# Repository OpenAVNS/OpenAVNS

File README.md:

# OpenAVNS

## Purpose
To develop an open-source, open-architecture auricular vagus nerve stimulator under a distributed development model.
 
Auricular vagus nerve stimulation (aVNS) is a method of neuromodulation that uses electrical pulses applied to nerves near the ear to create a vagus nerve response. This response can lead to reduced sympathetic (fight or flight) and increased parasympathetic (relaxation / everything ok) tone. Adjusting vagal tone using aVNS has been explored by clinical researchers for a number of potential therapeutic applications, including for depression [1], opioid withdraws [2], chronic pain [3], and gastrointestinal issues [4]. In addition, aVNS has been explored in wellness for applications such as stress reduction [5]. We believe an open-source, open-architecture aVNS system would be helpful for users, students, medical researchers, and community members around the world to explore aVNS and to learn more about developing neuromodulation devices under an open source model.
 
1. [Tan, Chaoren et. al. 2023](https://pubmed.ncbi.nlm.nih.gov/37230264/)  
2. [Tirado, Carlos F. et. al. 2022](https://pmc.ncbi.nlm.nih.gov/articles/PMC9385243/)  
3. [Duff, Irina T. et. al. 2024](https://pmc.ncbi.nlm.nih.gov/articles/PMC11543973/)  
4. [Veldman, Fleur et. al. 2025](https://pmc.ncbi.nlm.nih.gov/articles/PMC11769675/)  
5. [Sanches-Perez, Jesus et. al. 2023](https://pmc.ncbi.nlm.nih.gov/articles/PMC10512834/)  

## Principles of OpenAVNS
* _Openness_ – all source files, including code, PCB source files, CAD, and any documentation, available under permissive license
* _Accessibility_ – device developed using freely available tools (KiCad for PCBs, FreeCAD for enclosure, etc.); enclosure able to be 3D printed on home printer; PCBs use only common, off the shelf components and able to be taped out and assembled by a low-cost manufacturer; clear instructions are developed for building, flashing, and testing a device; low-cost, replaceable, commercially available electrodes are used to apply stimulation; apps should be developed on a platform that allows iOS and Android releases simultaneously
* _Wearability_ – device should be as small and unobtrusive as possible while maintaining openness and accessibility. Ideally, all electronics would fit behind the ear (similar to a behind-ear hearing aid or cochlear implant electronics) and can be comfortably worn for at least 30 minutes at a time
* _Effectiveness_ – the device should be capable of outputting stimulation with the same parameters as those used in clinical trials for at least 30 minutes. We note that OpenAVNS cannot be considered to be “effective” for any indication until it has been tested in a clinical trial.
* _Safety_ – the device’s electronics, firmware, software, and mechanical design should all be constructed with user safety in mind, and should be built to the standards of a medical device. We note that until OpenAVNS has been tested and cleared by a regulatory body for human use it cannot be considered “safe”; any use of the source files and documentation in the project must be done for educational purposes only and is done entirely at the user’s own risk. PLEASE DO NOT HURT YOURSELF!
 
## Proposed user needs and design inputs
| User Need | Design Input |
|-----------|--------------|
| The device shall apply neuromodulation to the auricular vagus branches at the tragus and cymba concha | Device shall provide two independent biphasic current-controlled stimulation outputs |
| The user shall easily activate, modify, and deactivate stimulation on the device | App shall allow adjustment of stimulation parameters (frequency, pulse width, amplitude) within specified ranges. <br><br> App shall allow initiating and stopping stimulation <br><br> Physical button on device to deactivate stimulation if needed <br><br> App shall be intuitive and easy to use |
| The user shall comfortably wear the device | Weight less than 40g <br><br> Device fits behind ear <br><br> Remains securely in place for 30 minutes of typical non-athletic activity without discomfort |
| The user shall apply neuromodulation typical of clinical studies reported in literature | Adjustable outputs between 1-50Hz, 100-500us pulse width, 0-2mA amplitude <br><br> Capable of outputting at maximum settings on one channel for a minimum of 30min |
| The device is open and accessible to a large range of users in different situations | Rechargeable by USB-C <br><br> Uses commercial off the shelf replaceable electrodes <br><br> App available on iOS and Android platforms |
| The device is safe to use | Device hardware prevents DC charge or amplitudes outside of the operating parameters from presenting at the electrode sites <br><br> Physical button on device to stop stimulation <br><br> Impedance measurement on output used to stop stimulation if electrodes are disconnected (short or open circuit) <br><br> Stimulation stops if wireless connection to app is interrupted <br><br> Firmware automatically stops stimulation after 30min regardless of other factors |

## Project Goals / Timeline
_2025_
* _August:_ set up project structure, onboard contributors, assign tasks, generate block diagrams of system
* _September:_ design and tape out first version of PCB, develop test firmware, generate proof of concept drawings / mock-ups for enclosure and user interface
* _October:_ test and document initial PCB and firmware for power draw, output integrity, and safety, develop initial app prototype, combine board needs and enclosure drawings to create CAD model
* _November:_ tape out second version of PCB designed for enclosure, conduct fit test, create alpha version of iOS and Android app
* _December:_ first system tests of prototype device (HW + FW + Enclosure + App)

## Contributors
Last updated 10/31/2025
* [Alex Baldwin](https://www.linkedin.com/in/alexbbaldwin/) - Founder, PCB schematics and layout
* [Amanda Cheung](https://www.linkedin.com/in/amandacheung8/) - Enclosure CAD
* [Maro Michailidou](https://www.linkedin.com/in/maro-michailidou/) - PCB Layout Review

## Disclaimer
The contents of this document, the OpenAVNS repository on GitHub, and any other documents or communication released by the OpenAVNS project (the “Materials”) are subject to revision. No representation or warranty, express or implied, is provided in relation to the accuracy, correctness, completeness, or reliability of the information, opinions, or conclusions expressed in this repository.

The Materials are experimental in nature and should be used with prudence and appropriate caution. Any use is voluntary and at your own risk.

The Materials are made available “as is” by the contributors to this repository (collectively, “Providers”). Providers expressly disclaim all warranties, express or implied, arising in connection with the Materials, or arising out of a course of performance, dealing, or trade usage, including, without limitation, any warranties of title, noninfringement, merchantability, or fitness for a particular purpose.

Any user of the Materials agrees to forever indemnify, defend, and hold harmless Providers from and against, and to waive any and all claims against Providers for any and all claims, suits, demands, liability, loss or damage whatsoever, including attorneys' fees, whether direct or consequential, on account of any loss, injury, death or damage to any person or (including without limitation all agents and employees of Providers and all property owned by, leased to or used by either Providers) or on account of any loss or damages to business or reputations or privacy of any persons, arising in whole or in part in any way from use of the Materials or in any way connected therewith or in any way related thereto.

The Materials, any related materials, and all intellectual property therein, are owned by Providers.

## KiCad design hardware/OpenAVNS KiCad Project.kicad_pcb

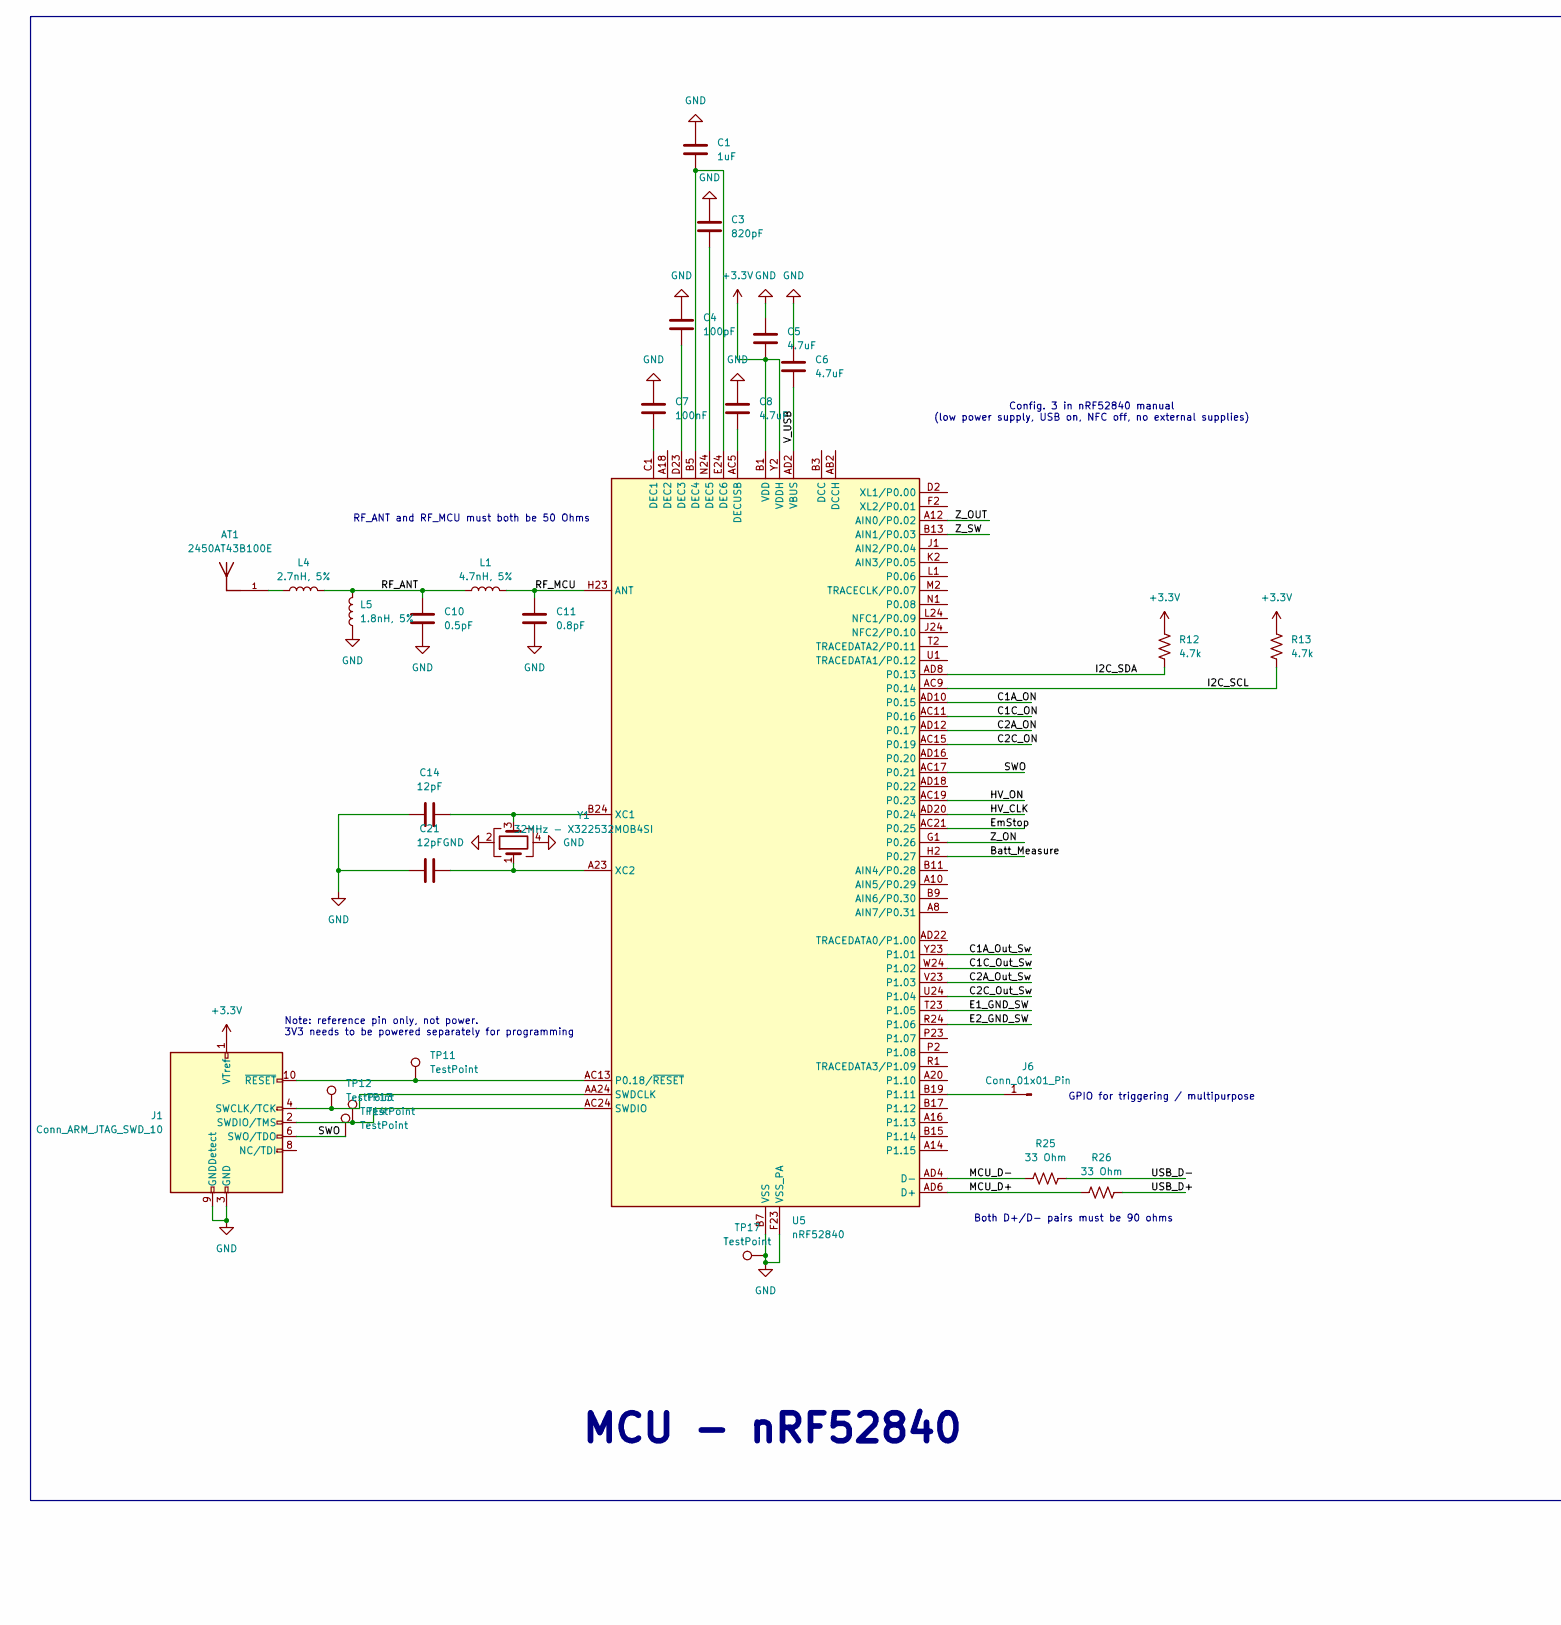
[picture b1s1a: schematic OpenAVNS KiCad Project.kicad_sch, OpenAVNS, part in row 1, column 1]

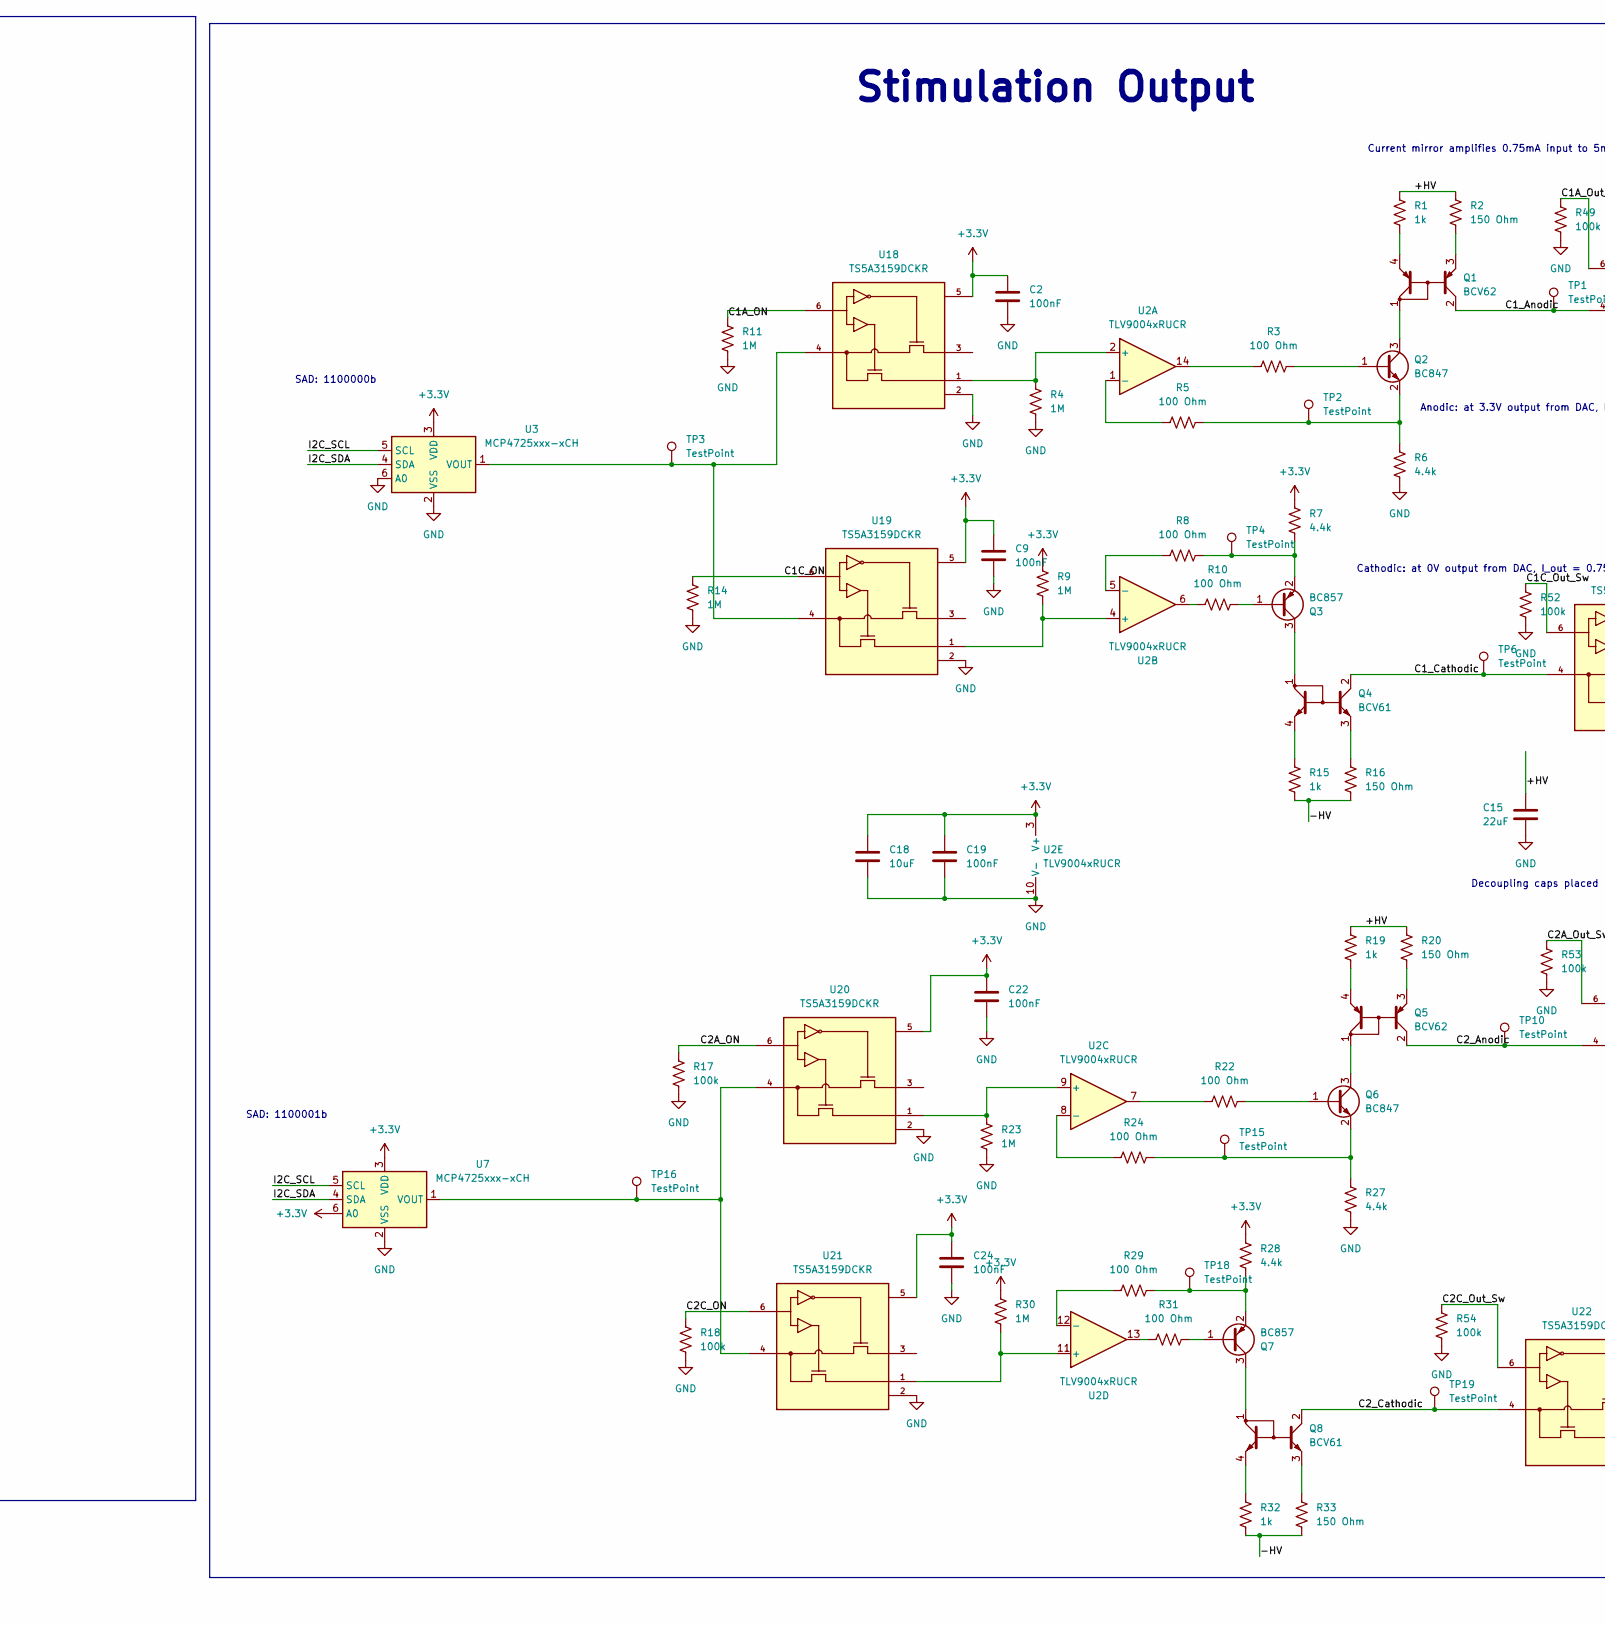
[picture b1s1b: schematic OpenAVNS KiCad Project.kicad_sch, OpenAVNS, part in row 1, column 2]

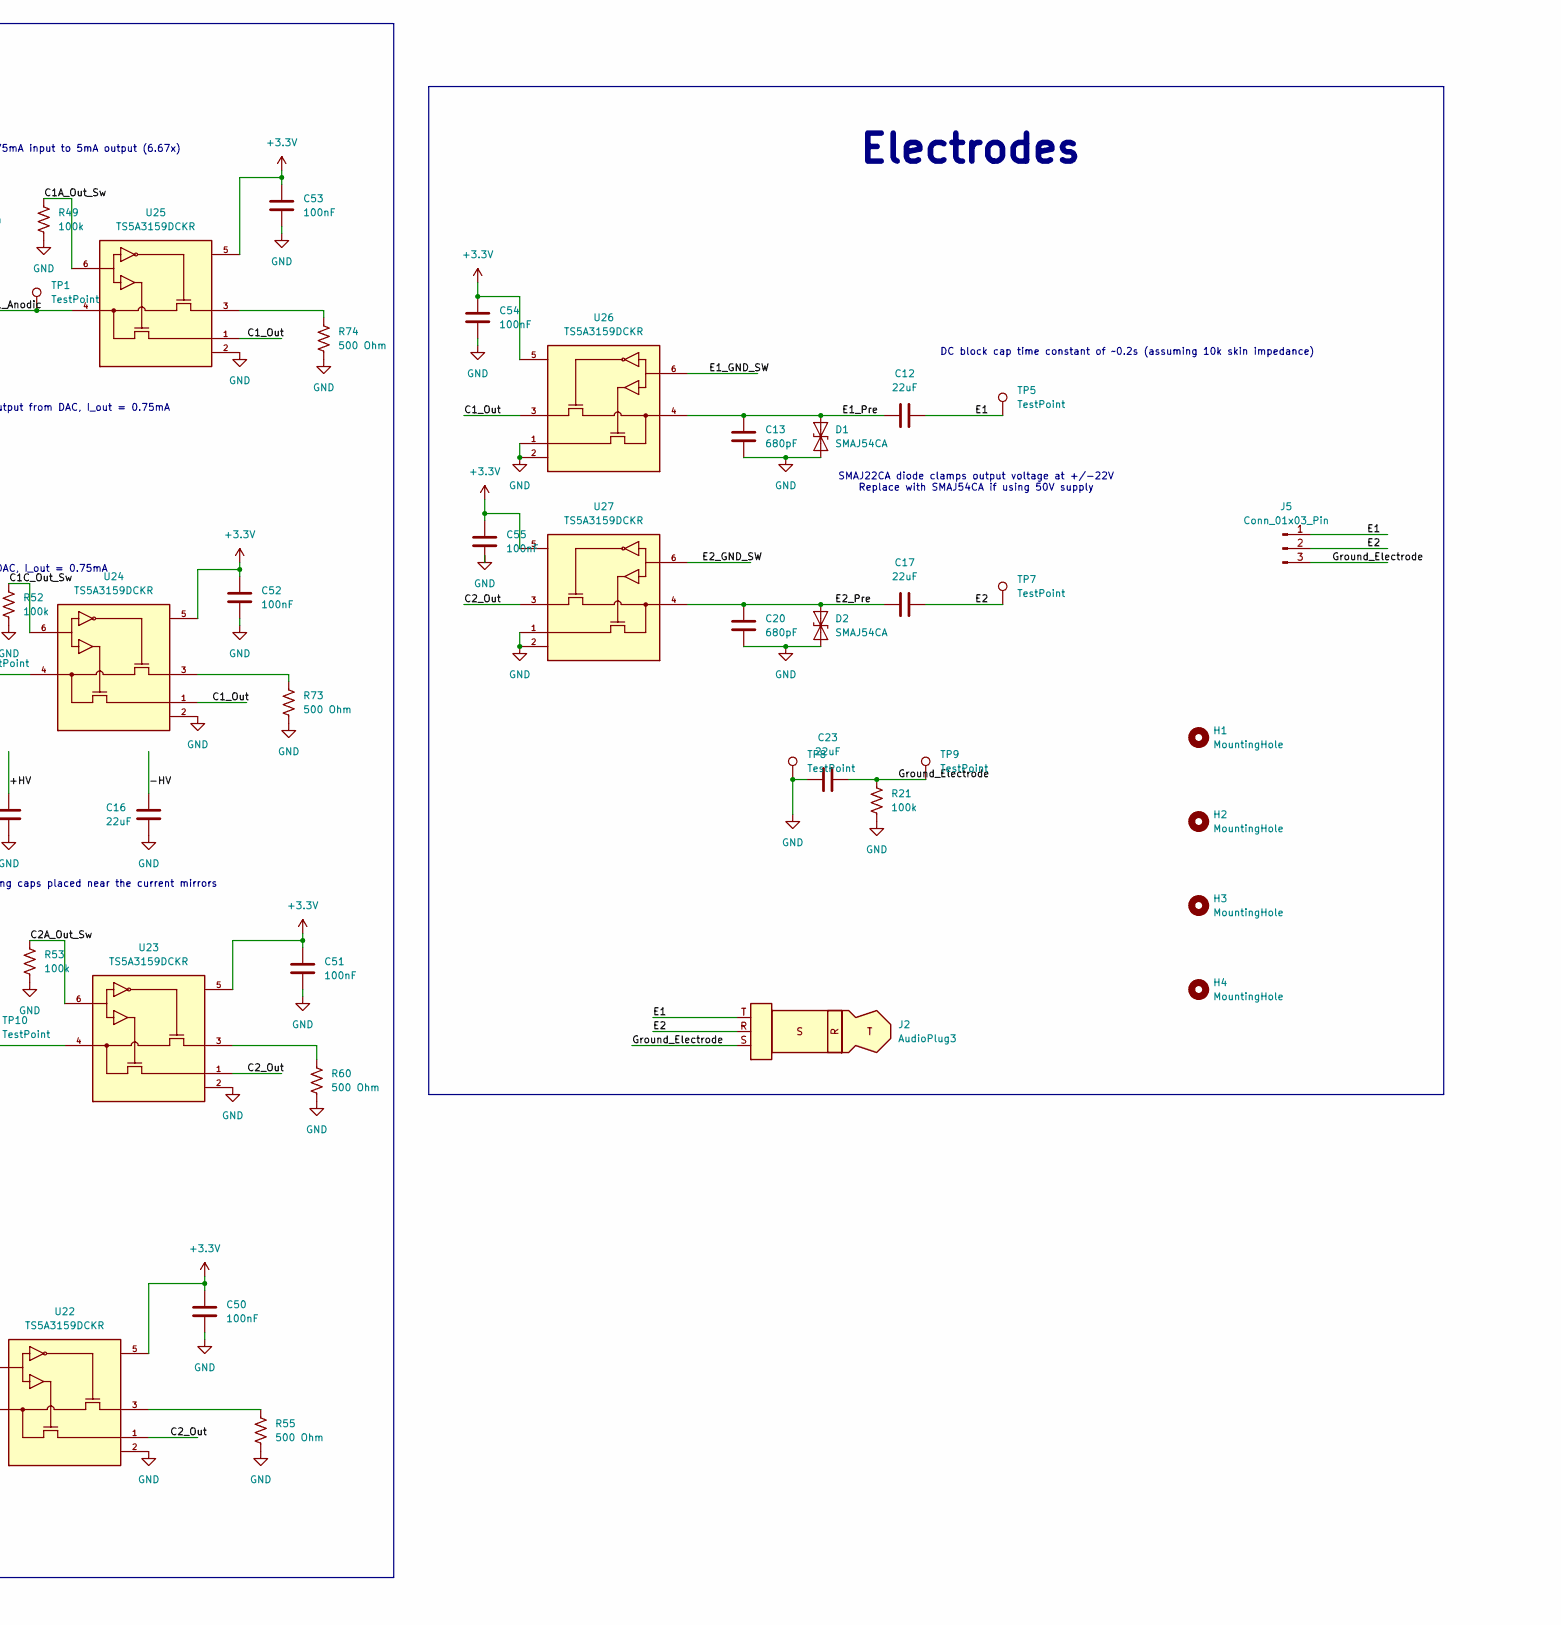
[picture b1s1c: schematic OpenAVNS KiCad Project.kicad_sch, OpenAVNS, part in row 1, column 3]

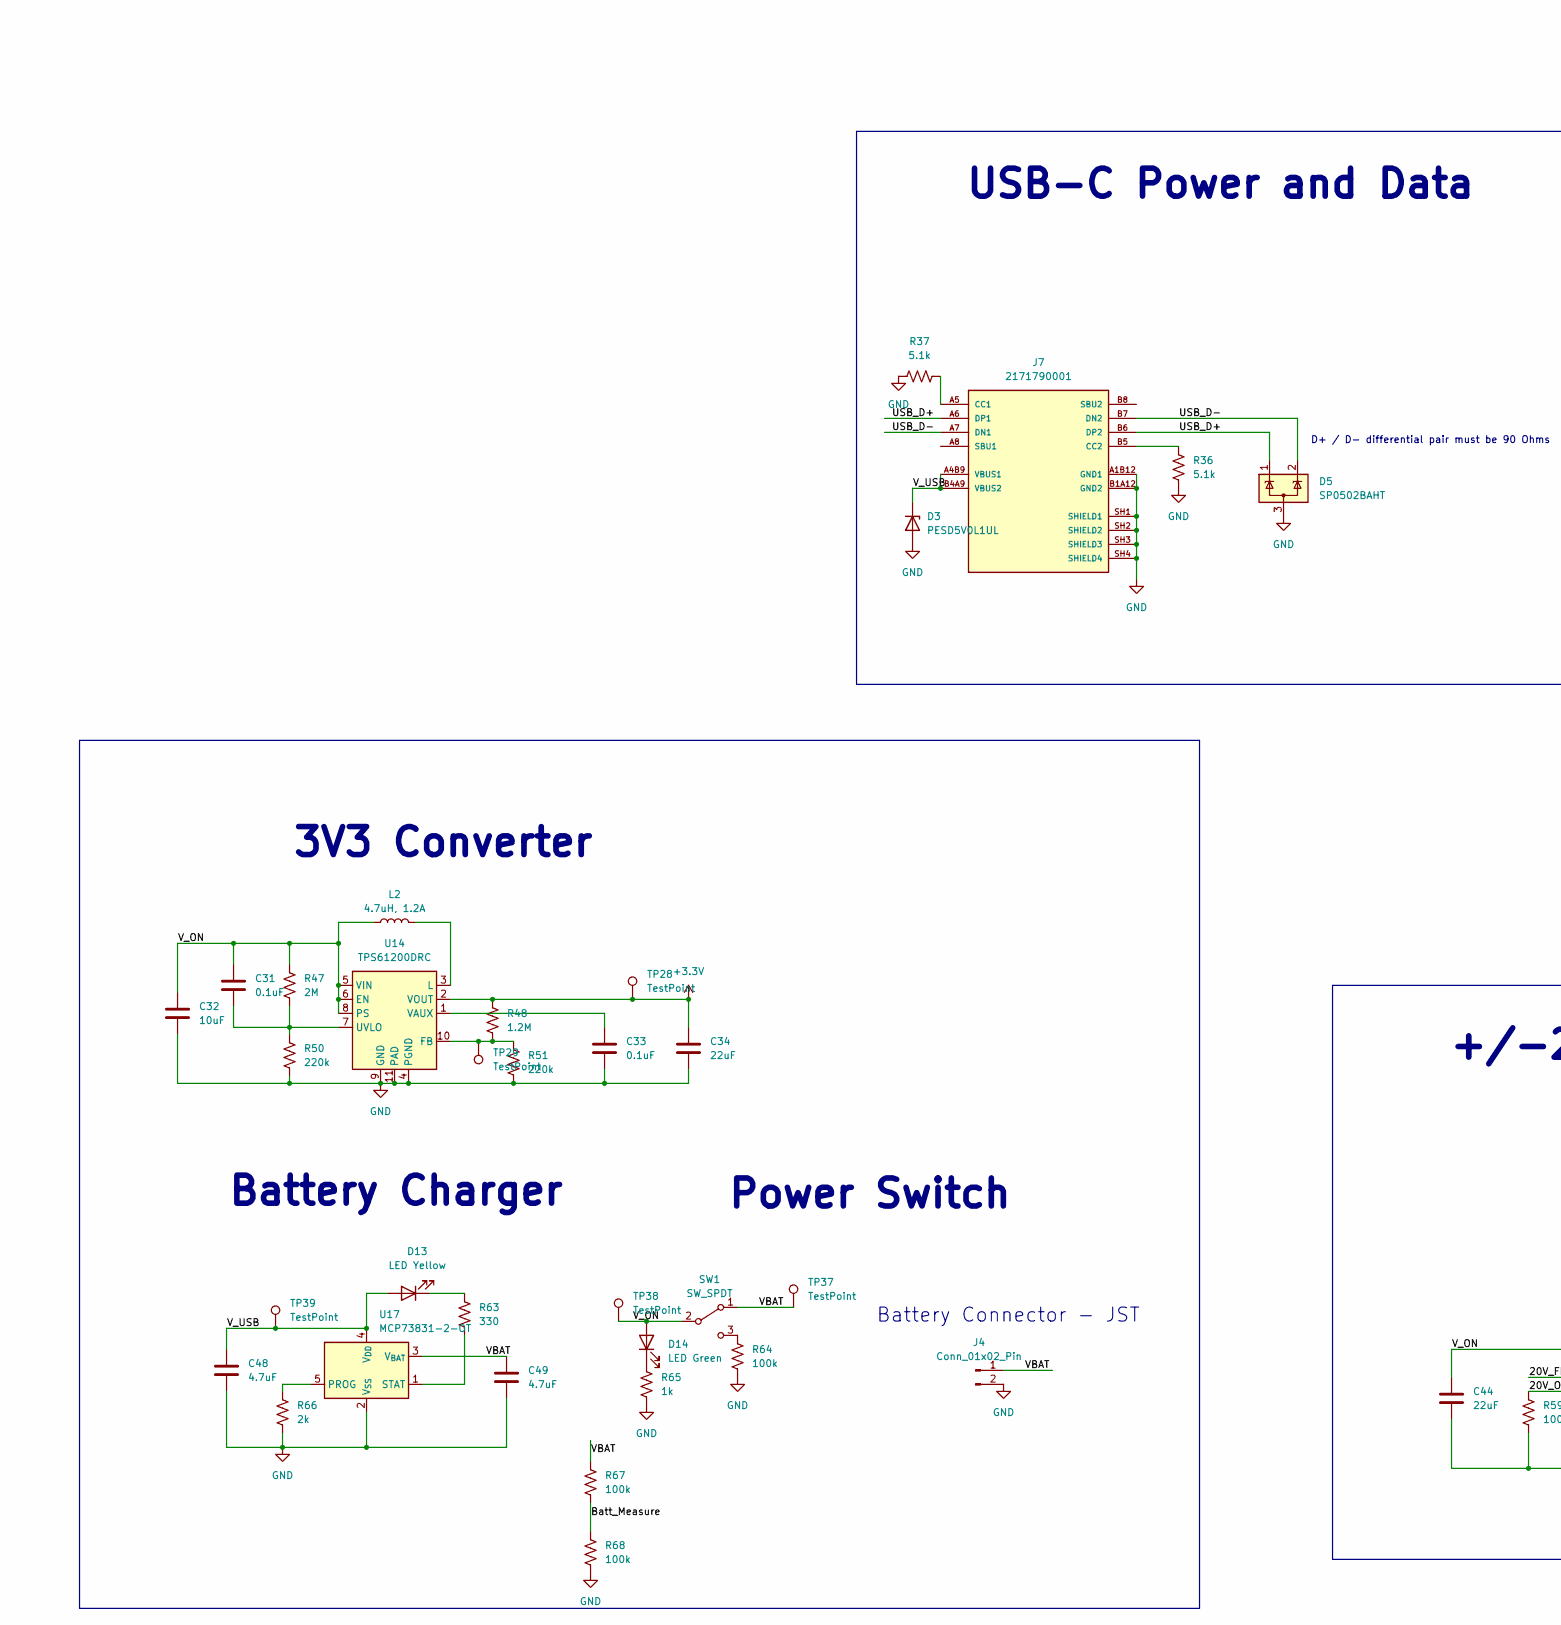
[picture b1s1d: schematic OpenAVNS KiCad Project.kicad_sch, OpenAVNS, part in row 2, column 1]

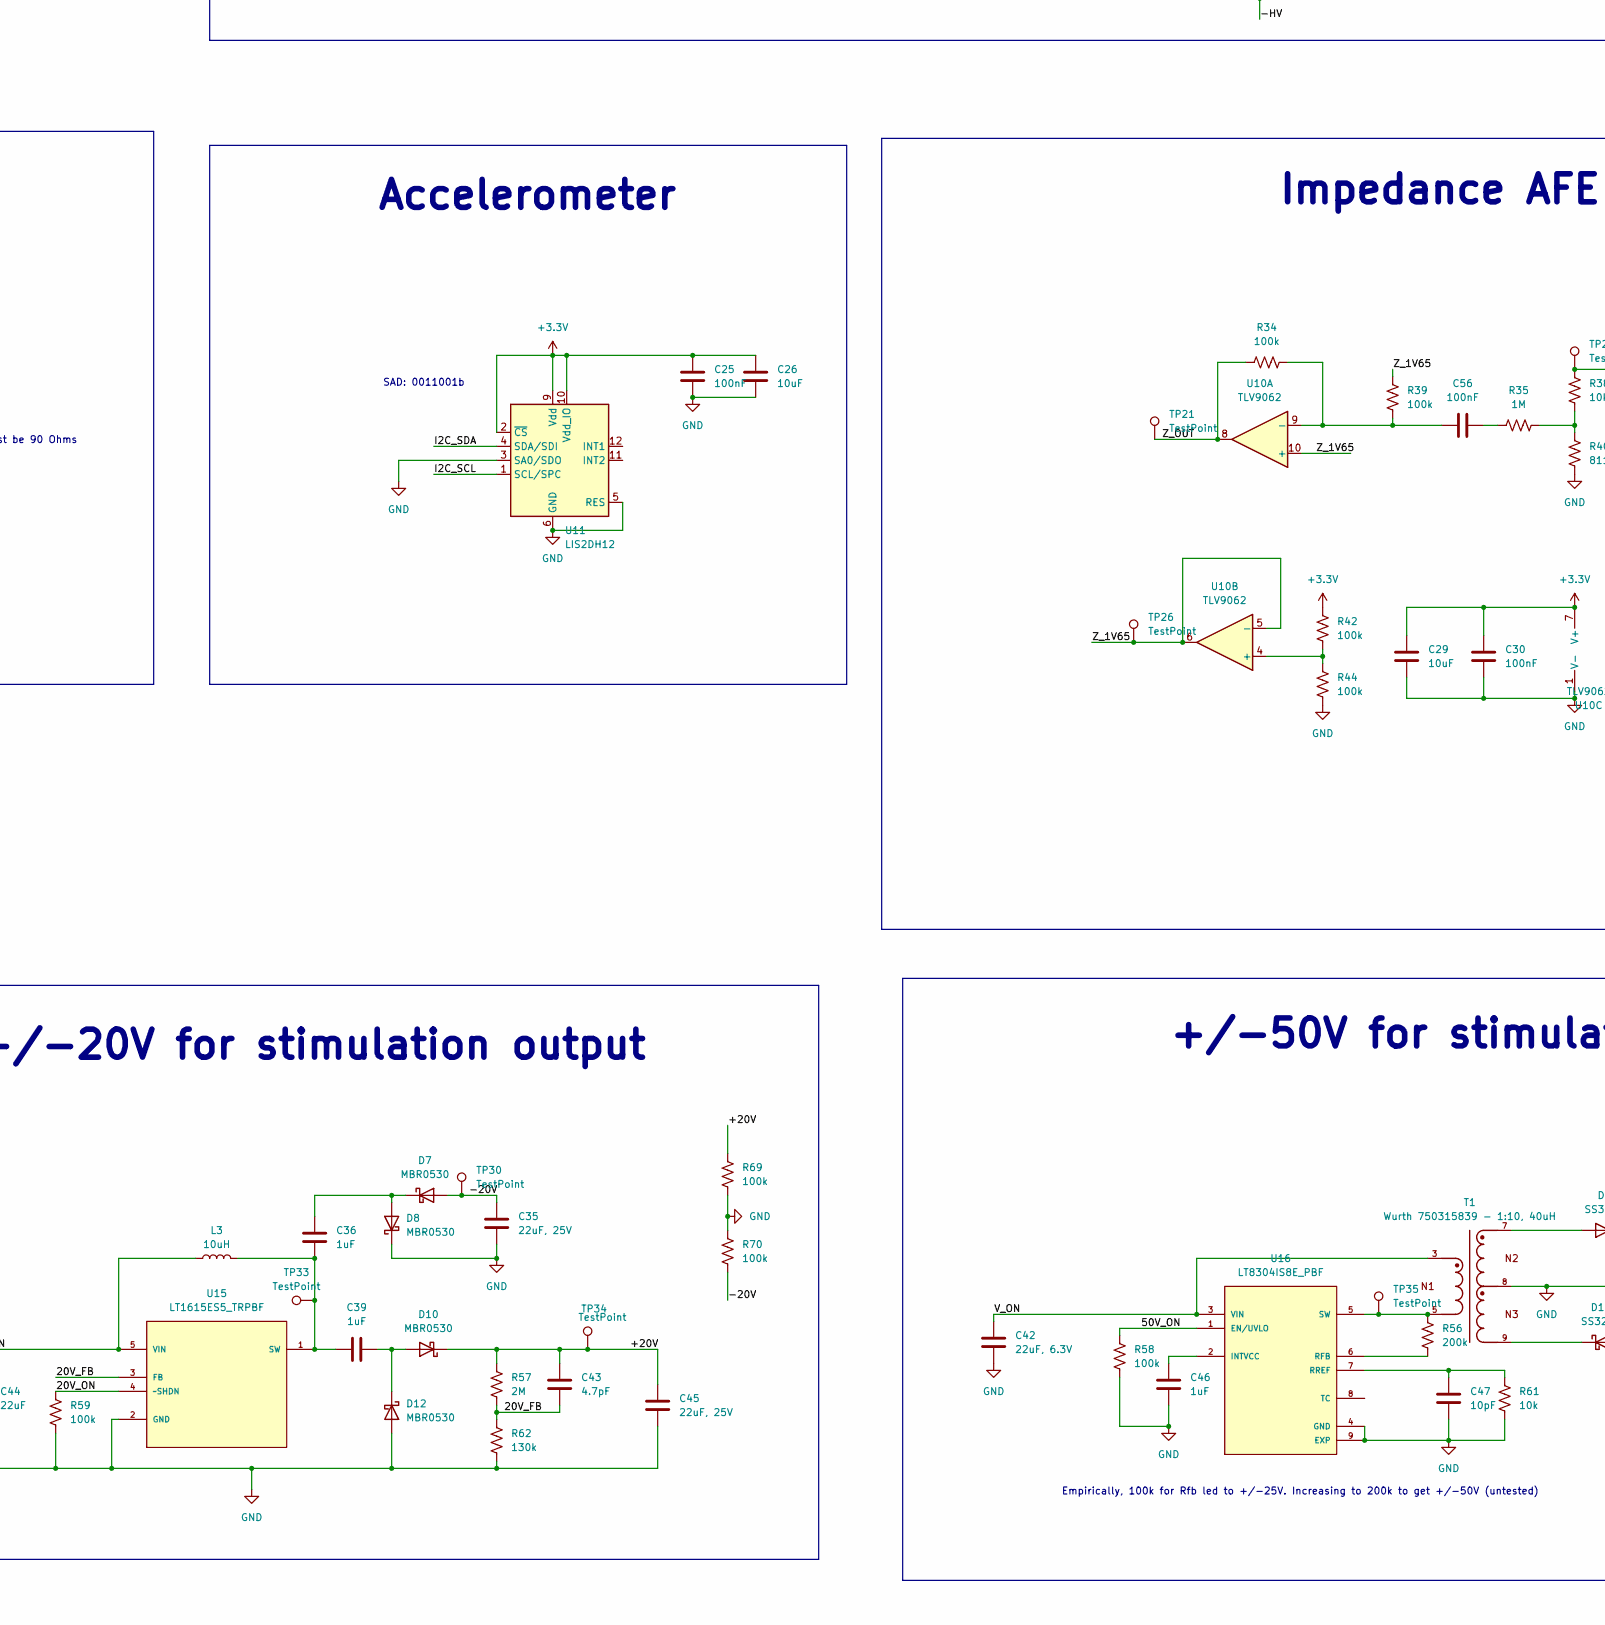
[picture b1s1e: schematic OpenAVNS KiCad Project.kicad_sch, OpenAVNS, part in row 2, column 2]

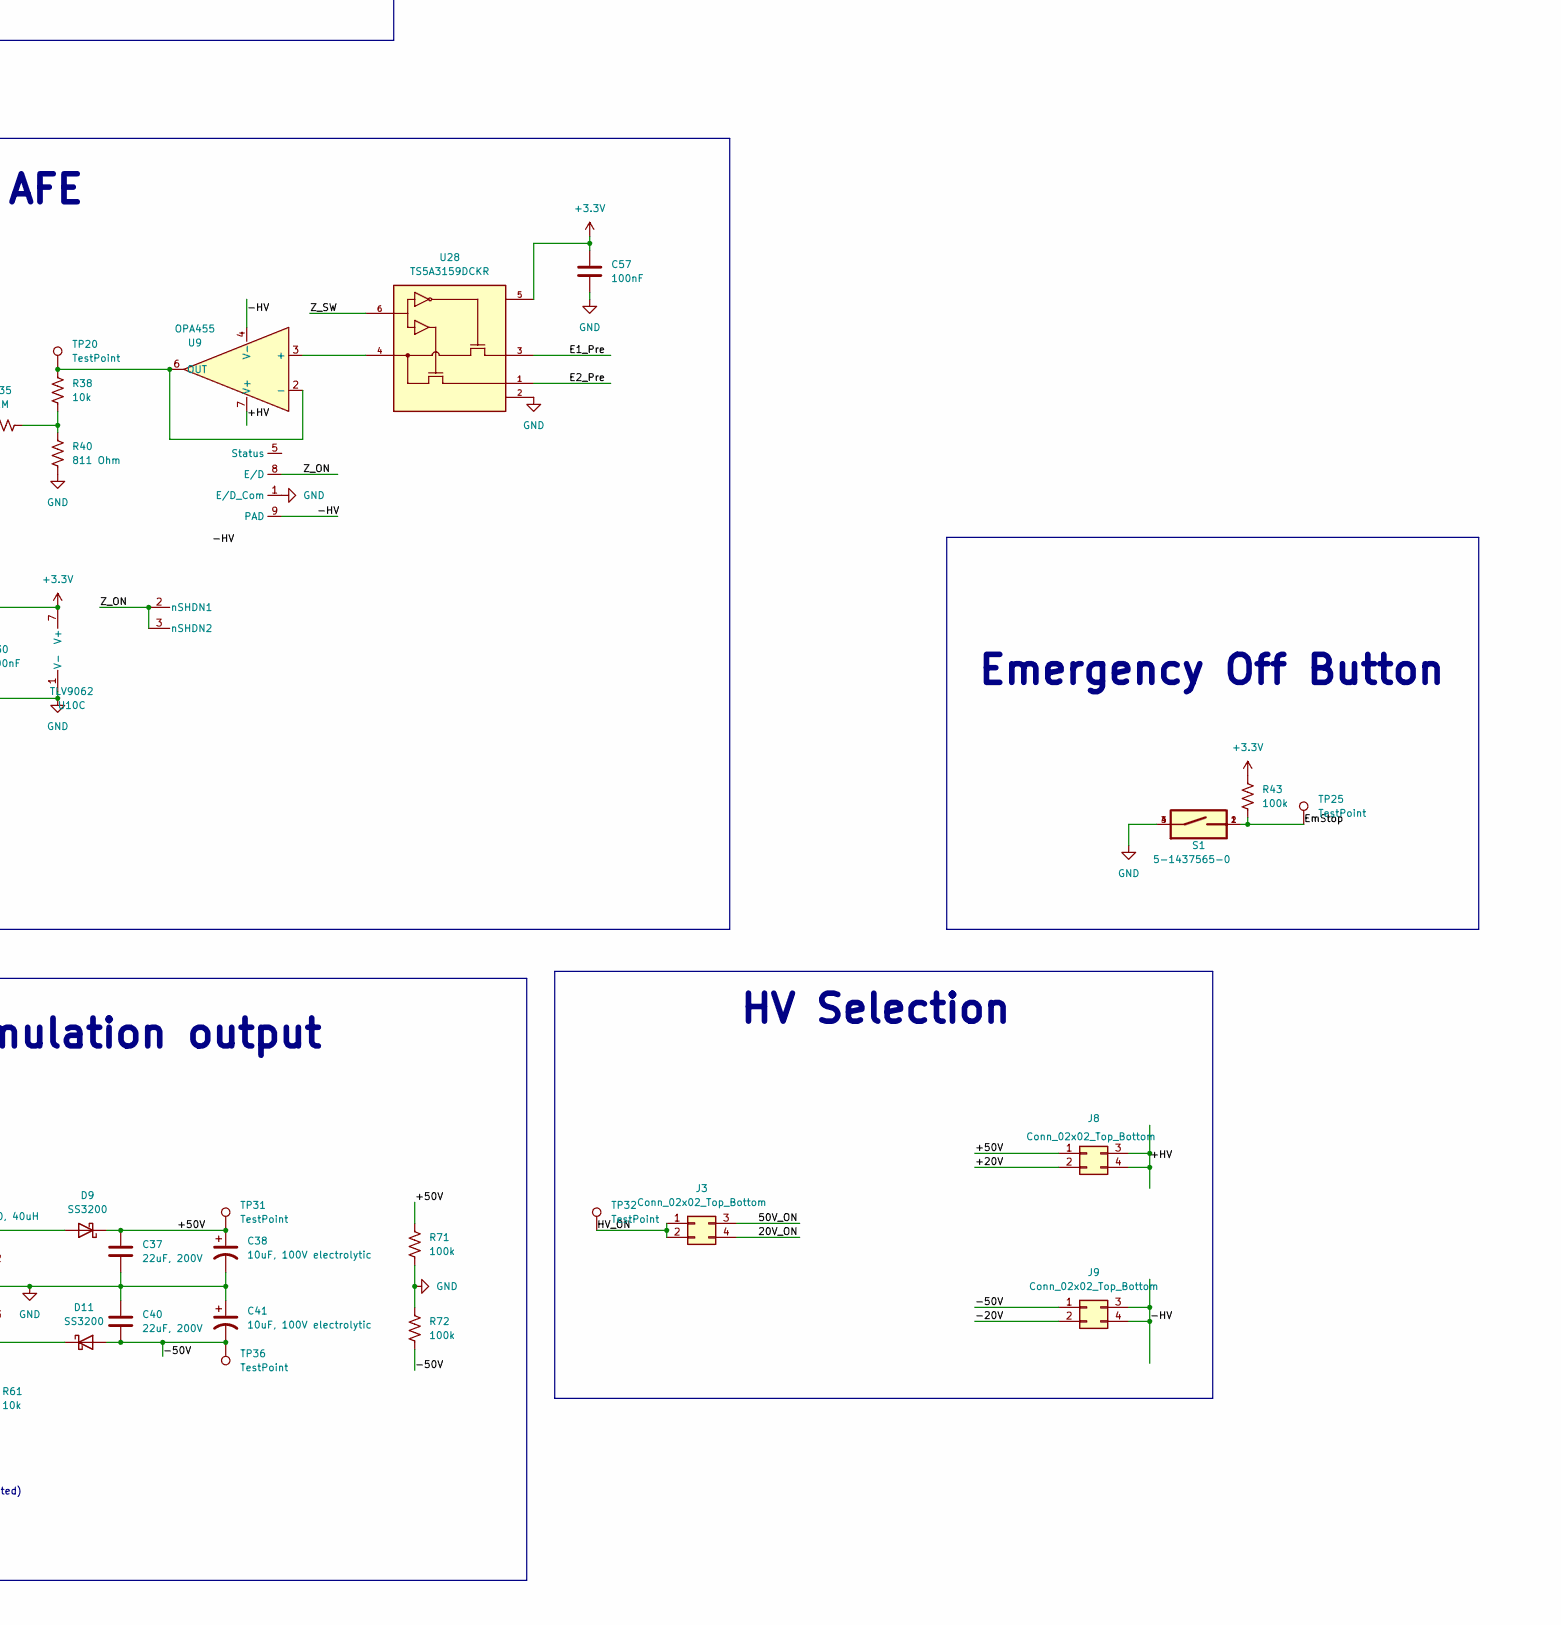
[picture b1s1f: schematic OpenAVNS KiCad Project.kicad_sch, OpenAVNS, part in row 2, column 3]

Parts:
AT1: 2450AT43B100E; ANTENNA_2450AT43B100E; PARTREV N/A
C1, C46: 1uF; C_0603_1608Metric
C2, C7, C9, C19, C22, C24, C25, C30, C50, C51, C52, C53, C54, C55, C56, C57: 100nF; C_0402_1005Metric
C3: 820pF; C_0402_1005Metric
C4: 100pF; C_0402_1005Metric
C5, C6, C8: 4.7uF; C_0603_1608Metric
C10: 0.5pF; C_0402_1005Metric
C11: 0.8pF; C_0402_1005Metric
C12, C15, C16, C17, C23: 22uF; C_1210_3225Metric
C13, C20: 680pF; C_0402_1005Metric
C14, C21: 12pF; C_0402_1005Metric
C18, C26, C29: 10uF; C_0603_1608Metric
C31, C33: 0.1uF; C_0603_1608Metric
C32: 10uF; C_0805_2012Metric
C34, C44: 22uF; C_0805_2012Metric
C35, C45: 22uF, 25V; C_1210_3225Metric
C36, C39: 1uF; C_0805_2012Metric
C37, C40: 22uF, 200V; C_1210_3225Metric
C38, C41: 10uF, 100V electrolytic; CP_Radial_D6.3mm_P2.50mm
C42: 22uF, 6.3V; C_0805_2012Metric
C43: 4.7pF; C_0805_2012Metric
C47: 10pF; C_0603_1608Metric
C48, C49: 4.7uF; C_0805_2012Metric
D1, D2: SMAJ54CA; D_SMA
D3: PESD5V0L1UL; D_SOD-882
D5: SP0502BAHT; SOT-23
D7, D8, D10, D12: MBR0530; D_SOD-123
D9, D11: SS3200; D_SMA
D13: LED Yellow; LED_0402_1005Metric
D14: LED Green; LED_0402_1005Metric
H1, H2, H3, H4: MountingHole; MountingHole_3.2mm_M3_DIN965
J1: Conn_ARM_JTAG_SWD_10; PinHeader_2x05_P1.27mm_Vertical_SMD
J2: AudioPlug3; Jack_3.5mm_CUI_SJ-3523-SMT_Horizontal
J3, J8, J9: Conn_02x02_Top_Bottom; PinSocket_2x02_P2.54mm_Vertical
J4: Conn_01x02_Pin; PinHeader_1x02_P2.00mm_Vertical
J5: Conn_01x03_Pin; PinHeader_1x03_P2.54mm_Vertical
J6: Conn_01x01_Pin; PinHeader_1x01_P1.00mm_Horizontal
J7: 2171790001; MOLEX_2171790001; PARTREV A1
L1: 4.7nH, 5%; L_0402_1005Metric
L2: 4.7uH, 1.2A; L_1008_2520Metric_Pad1.43x2.20mm_HandSolder
L3: 10uH; L_7.3x7.3_H3.5
L4: 2.7nH, 5%; L_0402_1005Metric
L5: 1.8nH, 5%; L_0402_1005Metric
Q1, Q5: BCV62; SOT-143
Q2, Q6: BC847; SOT-23
Q3, Q7: BC857; SOT-23
Q4, Q8: BCV61; SOT-143
R1, R15, R19, R32: 1k; C_0805_2012Metric
R2, R16, R20, R33: 150 Ohm; C_0805_2012Metric
R3, R5, R8, R10, R22, R24, R29, R31: 100 Ohm; C_0402_1005Metric
R4, R9, R11, R14, R23, R30: 1M; C_0402_1005Metric
R6, R7, R27, R28: 4.4k; C_0805_2012Metric
R12, R13: 4.7k; R_0402_1005Metric
R17, R18, R49, R52, R53, R54: 100k; C_0402_1005Metric
R21, R34, R39, R42, R43, R44, R58, R59, R64, R67, R68: 100k; R_0402_1005Metric
R25, R26: 33 Ohm; R_0402_1005Metric
R35: 1M; R_0402_1005Metric
R36, R37: 5.1k; R_0402_1005Metric
R38: 10k; R_1206_3216Metric
R40: 811 Ohm; R_1206_3216Metric
R47: 2M; R_0402_1005Metric
R48: 1.2M; R_0402_1005Metric
R50, R51: 220k; R_0402_1005Metric
R55, R60, R73, R74: 500 Ohm; C_0402_1005Metric
R56: 200k; R_0805_2012Metric_Pad1.20x1.40mm_HandSolder
R57: 2M; R_0603_1608Metric
R61: 10k; R_0805_2012Metric_Pad1.20x1.40mm_HandSolder
R62: 130k; R_0603_1608Metric
R63: 330; R_0402_1005Metric
R65: 1k; R_0402_1005Metric
R66: 2k; R_0402_1005Metric
R69, R70, R71, R72: 100k; R_0805_2012Metric_Pad1.20x1.40mm_HandSolder
S1: 5-1437565-0; SW_SPST_PTS647_Sx38; PARTREV V
SW1: SW_SPDT; SW_SPDT_CK_JS102011SAQN
T1: Wurth 750315839 - 1:10, 40uH; WE-FLYLT_EP13_5465
TP1, TP2, TP3, TP4, TP5, TP6, TP7, TP8, TP9, TP10, TP11, TP12, TP13, TP14, TP15, TP16, TP17, TP18, TP19, TP20, TP21, TP25, TP26, TP28, TP29, TP30, TP31, TP32, TP33, TP34, TP35, TP36, TP37, TP38, TP39: TestPoint; TestPoint_Pad_D2.0mm
U2: TLV9004xRUCR; Texas_S-PX2QFN-14
U3, U7: MCP4725xxx-xCH; SOT-23-6
U5: nRF52840; Nordic_AQFN-73-1EP_7x7mm_P0.5mm
U9: OPA455; TI_SO-PowerPAD-8_ThermalVias
U10: TLV9062; QFN50P200X150X40-10N
U11: LIS2DH12; LGA-12_2x2mm_P0.5mm
U14: TPS61200DRC; Texas_S-PVSON-N10_ThermalVias
U15: LT1615ES5_TRPBF; SOT95P280X145-5N; MPN LT1615ES5#PBF
U16: LT8304IS8E_PBF; SOIC127P599X175-9N; PARTREV LT0217_REV_A
U17: MCP73831-2-OT; SOT-23-5
U18, U19, U20, U21, U22, U23, U24, U25, U26, U27, U28: TS5A3159DCKR; SOT65P210X110-6N; PARTREV D
Y1: 32MHz - X322532MOB4SI; Crystal_SMD_3225-4Pin_3.2x2.5mm

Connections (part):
+3.3V: C2.1, C5.1, C9.1, C18.1, C19.1, C22.1, C24.1, C25.1, C26.1, C29.1, C30.1, C34.1, C50.1, C51.1, C52.1, C53.1, C54.1, C55.1, C57.1, J1.1 (VTref), R7.2, R9.2, R12.2, R13.2, R28.2, R30.2, R42.2, R43.1, R48.1, TP28.1 (1_1), U2.3 (V+), U3.3 (VDD), U5.A22 (VDD), U5.AD14 (VDD), U5.AD23 (VDD), U5.B1 (VDD), U5.W1 (VDD), U5.Y2 (VDDH), U7.3 (VDD), U7.6 (A0), U10.7 (V+), U11.2 (~CS), U11.9 (Vdd), U11.10 (Vdd_IO), U14.2 (VOUT), U18.5, U19.5, U20.5, U21.5, U22.5, U23.5, U24.5, U25.5, U26.5, U27.5, U28.5
/20V_FB: C43.2, R57.1, R62.2, U15.3 (FB)
/20V_ON: J3.4, R59.2, U15.4 (~SHDN)
/50V_ON: J3.3, R58.2, U16.1 (EN/UVLO)
/+20V: C43.1, C45.1, D10.1 (K), J8.2, R57.2, R69.2, TP34.1 (1_1)
/+50V: C37.1, C38.1, D9.1 (K), J8.1, R71.2, TP31.1 (1_1)
/+HV: C15.1, J8.3, J8.4, R1.2, R2.2, R19.2, R20.2, U9.7 (V+)
/-20V: C35.1, D7.2 (A), J9.2, R70.1, TP30.1 (1_1)
/-50V: C40.2, C41.2, D11.2 (A), J9.1, R72.1, TP36.1 (1_1)
/-HV: C16.1, J9.3, J9.4, R15.1, R16.1, R32.1, R33.1, U9.4 (V-), U9.9 (PAD)
/Batt_Measure: R67.1, R68.2, U5.H2 (P0.27)
/C1A_ON: R11.2, U5.AD10 (P0.15), U18.6
/C1A_Out_Sw: R49.2, U5.Y23 (P1.01), U25.6
/C1C_ON: R14.2, U5.AC11 (P0.16), U19.6
/C1C_Out_Sw: R52.2, U5.W24 (P1.02), U24.6
/C1_Anodic: Q1.2 (C1), TP1.1 (1_1), U25.4
/C1_Cathodic: Q4.2 (C1), TP6.1 (1_1), U24.4
/C1_Out: U24.1, U25.1, U26.3
/C2A_ON: R17.2, U5.AD12 (P0.17), U20.6
/C2A_Out_Sw: R53.2, U5.V23 (P1.03), U23.6
/C2C_ON: R18.2, U5.AC15 (P0.19), U21.6
/C2C_Out_Sw: R54.2, U5.U24 (P1.04), U22.6
/C2_Anodic: Q5.2 (C1), TP10.1 (1_1), U23.4
/C2_Cathodic: Q8.2 (C1), TP19.1, U22.4
/C2_Out: U22.1, U23.1, U27.3
/E1: C12.2, J2.T, J5.1, TP5.1 (1_1)
/E1_GND_SW: U5.T23 (P1.05), U26.6
/E1_Pre: C12.1, C13.1, D1.2 (A2), U26.4, U28.3
/E2: C17.2, J2.R, J5.2, TP7.1 (1_1)
/E2_GND_SW: U5.R24 (P1.06), U27.6
/E2_Pre: C17.1, C20.1, D2.2 (A2), U27.4, U28.1
/EmStop: R43.2, S1.1, S1.2, TP25.1 (1_1), U5.AC21 (P0.25)
/Ground_Electrode: C23.2, J2.S, J5.3, R21.1, TP9.1 (1_1)
/HV_CLK: U5.AD20 (P0.24)
/HV_ON: J3.1, J3.2, TP32.1 (1_1), U5.AC19 (P0.23)
/I2C_SCL: R13.1, U3.5 (SCL), U5.AC9 (P0.14), U7.5 (SCL), U11.1 (SCL/SPC)
/I2C_SDA: R12.1, U3.4 (SDA), U5.AD8 (P0.13), U7.4 (SDA), U11.4 (SDA/SDI)
/MCU_D+: R26.2, U5.AD6 (D+)
/MCU_D-: R25.2, U5.AD4 (D-)
/RF_ANT: C10.2, L1.1, L4.2, L5.2
/RF_MCU: C11.2, L1.2, U5.H23 (ANT)
/SWO: J1.6 (SWO/TDO), TP14.1 (1_1), U5.AC17 (P0.21)
/USB_D+: D5.1 (K), J7.A6 (DP1), J7.B6 (DP2), R26.1
/USB_D-: D5.2 (K), J7.A7 (DN1), J7.B7 (DN2), R25.1
/VBAT: C49.1, J4.1, R67.2, SW1.1 (A), TP37.1 (1_1), U17.3 (V_{BAT})
/V_ON: C31.1, C32.1, C42.1, C44.1, D14.2 (A), L2.1, L3.1, R47.1, SW1.2 (B), T1.3, TP38.1 (1_1), U14.5 (VIN), U14.6 (EN), U14.8 (PS), U15.5 (VIN), U16.3 (VIN)
/V_USB: C6.1, C48.1, D3.1 (K), D13.2 (A), J7.A4B9 (VBUS1), J7.B4A9 (VBUS2), TP39.1 (1_1), U5.AD2 (VBUS), U17.4 (V_{DD})
/Z_1V65: R39.2, TP26.1 (1_1), U10.5 (-), U10.6, U10.10 (+)
/Z_ON: U5.G1 (P0.26), U9.8 (E/D), U10.2 (nSHDN1), U10.3 (nSHDN2)
/Z_OUT: R34.1, TP21.1 (1_1), U5.A12 (AIN0/P0.02), U10.8
/Z_SW: U5.B13 (AIN1/P0.03), U28.6
GND: C1.2, C2.2, C3.2, C4.2, C5.2, C6.2, C7.2, C8.2, C9.2, C10.1, C11.1, C13.2, C14.1, C15.2, C16.2, C18.2, C19.2, C20.2, C21.2, C22.2, C23.1, C24.2, C25.2, C26.2, C29.2, C30.2, C32.2, C33.2, C34.2, C35.2, C37.2, C38.2, C40.1, C41.1, C42.2, C44.2, C45.2, C46.2, C47.2, C48.2, C49.2, C50.2, C51.2, C52.2, C53.2, C54.2, C55.2, C57.2, D1.1 (A1), D2.1 (A1), D3.2 (A), D5.3 (A), D8.1 (K), D12.2 (A), J1.3 (GND), J1.5 (GND), J1.9 (GNDDetect), J4.2, J7.A1B12 (GND1), J7.B1A12 (GND2), J7.SH1 (SHIELD1), J7.SH2 (SHIELD2), J7.SH3 (SHIELD3), J7.SH4 (SHIELD4), L5.1, R4.1, R6.1, R11.1, R14.1, R17.1, R18.1, R21.2, R23.1, R27.1, R36.2, R37.2, R40.2, R44.1, R49.1, R50.2, R51.2, R52.1, R53.1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
unnamed: AT1.1, L4.1
unnamed: C56.2, R35.1
unnamed: C36.1, D7.1 (K), D8.2 (A)
unnamed: D9.2 (A), T1.7
unnamed: C39.2, D10.2 (A), D12.1 (K)
unnamed: D11.1 (K), T1.9
unnamed: D13.1 (K), R63.2
unnamed: D14.1 (K), R65.2
unnamed: J1.4 (SWCLK/TCK), TP12.1 (1_1), U5.AA24 (SWDCLK)
unnamed: J1.2 (SWDIO/TMS), TP13.1 (1_1), U5.AC24 (SWDIO)
unnamed: J1.10 (~RESET), TP11.1 (1_1), U5.AC13 (P0.18/~RESET)
unnamed: J6.1 (Pin_1_1), U5.B19 (P1.11)
unnamed: J7.A5 (CC1), R37.1
unnamed: J7.B5 (CC2), R36.1
unnamed: Q1.1 (C2), Q2.3 (C)
unnamed: Q1.3 (E1), R2.1
unnamed: Q1.4 (E2), R1.1
unnamed: Q2.1 (B), R3.1
unnamed: Q2.2 (E), R5.2, R6.2, TP2.1 (1_1)
unnamed: Q3.1 (B), R10.2
unnamed: Q3.3 (C), Q4.1 (C2)
unnamed: Q3.2 (E), R7.1, R8.2, TP4.1 (1_1)
unnamed: Q4.3 (E1), R16.2
unnamed: Q4.4 (E2), R15.2
unnamed: Q5.1 (C2), Q6.3 (C)
unnamed: Q5.3 (E1), R20.1
unnamed: Q5.4 (E2), R19.1
unnamed: Q6.1 (B), R22.1
unnamed: Q6.2 (E), R24.2, R27.2, TP15.1 (1_1)
unnamed: Q7.1 (B), R31.2
unnamed: Q7.3 (C), Q8.1 (C2)
unnamed: Q7.2 (E), R28.1, R29.2, TP18.1 (1_1)
unnamed: Q8.3 (E1), R33.2
unnamed: Q8.4 (E2), R32.2
unnamed: R3.2, U2.14
unnamed: R10.1, U2.6
unnamed: R22.2, U2.7
unnamed: R31.1, U2.13
unnamed: R35.2, R38.2, R40.1
unnamed: R55.2, U22.3
unnamed: R60.2, U23.3
unnamed: R73.2, U24.3
unnamed: R74.2, U25.3
unnamed: R64.2, SW1.3 (C)
unnamed: R4.2, U2.2 (+), U18.1
unnamed: R5.1, U2.1 (-)
unnamed: R9.1, U2.4 (+), U19.1
unnamed: R8.1, U2.5 (-)
unnamed: R23.2, U2.9 (+), U20.1
unnamed: R24.1, U2.8 (-)
unnamed: R30.1, U2.11 (+), U21.1
unnamed: R29.1, U2.12 (-)
unnamed: TP3.1 (1_1), U3.1 (VOUT), U18.4, U19.4
unnamed: C7.1, U5.C1 (DEC1)
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
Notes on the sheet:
3V3 Converter
SAD: 0011001b
MCU - nRF52840
HV Selection
Battery Charger
Anodic: at 3.3V output from DAC, I_out = 0.75mA
Config. 3 in nRF52840 manual (low power supply, USB on, NFC off, no external supplies)
Decoupling caps placed near the current mirrors
Impedance AFE
SMAJ22CA diode clamps output voltage at +/-22V Replace with SMAJ54CA if using 50V supply
SAD: 1100001b
Stimulation Output
Power Switch
Cathodic: at 0V output from DAC, I_out = 0.75mA
Battery Connector - JST
+/-50V for stimulation output
Electrodes
Current mirror amplifies 0.75mA input to 5mA output (6.67x)
+/-20V for stimulation output
DC block cap time constant of ~0.2s (assuming 10k skin impedance)
Accelerometer
Both D+/D- pairs must be 90 ohms
Note: reference pin only, not power. 3V3 needs to be powered separately for programming
GPIO for triggering / multipurpose
D+ / D- differential pair must be 90 Ohms
Empirically, 100k for Rfb led to +/-25V. Increasing to 200k to get +/-50V (untested)
SAD: 1100000b
Emergency Off Button
RF_ANT and RF_MCU must both be 50 Ohms
USB-C Power and Data
